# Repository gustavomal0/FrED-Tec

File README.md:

# Proyecto FrED

Este repositorio contiene todos los archivos relacionados con el Proyecto FrED, incluyendo diseños CAD, electrónica y firmware.

## Estructura de directorios

- CAD/: Contiene todos los modelos 3D, dibujos y otros archivos de diseño.
- Electrónica/: Incluye esquemas, diseños de PCB y documentación relacionada.
- Firmware/: Contiene el código fuente y los archivos del firmware.

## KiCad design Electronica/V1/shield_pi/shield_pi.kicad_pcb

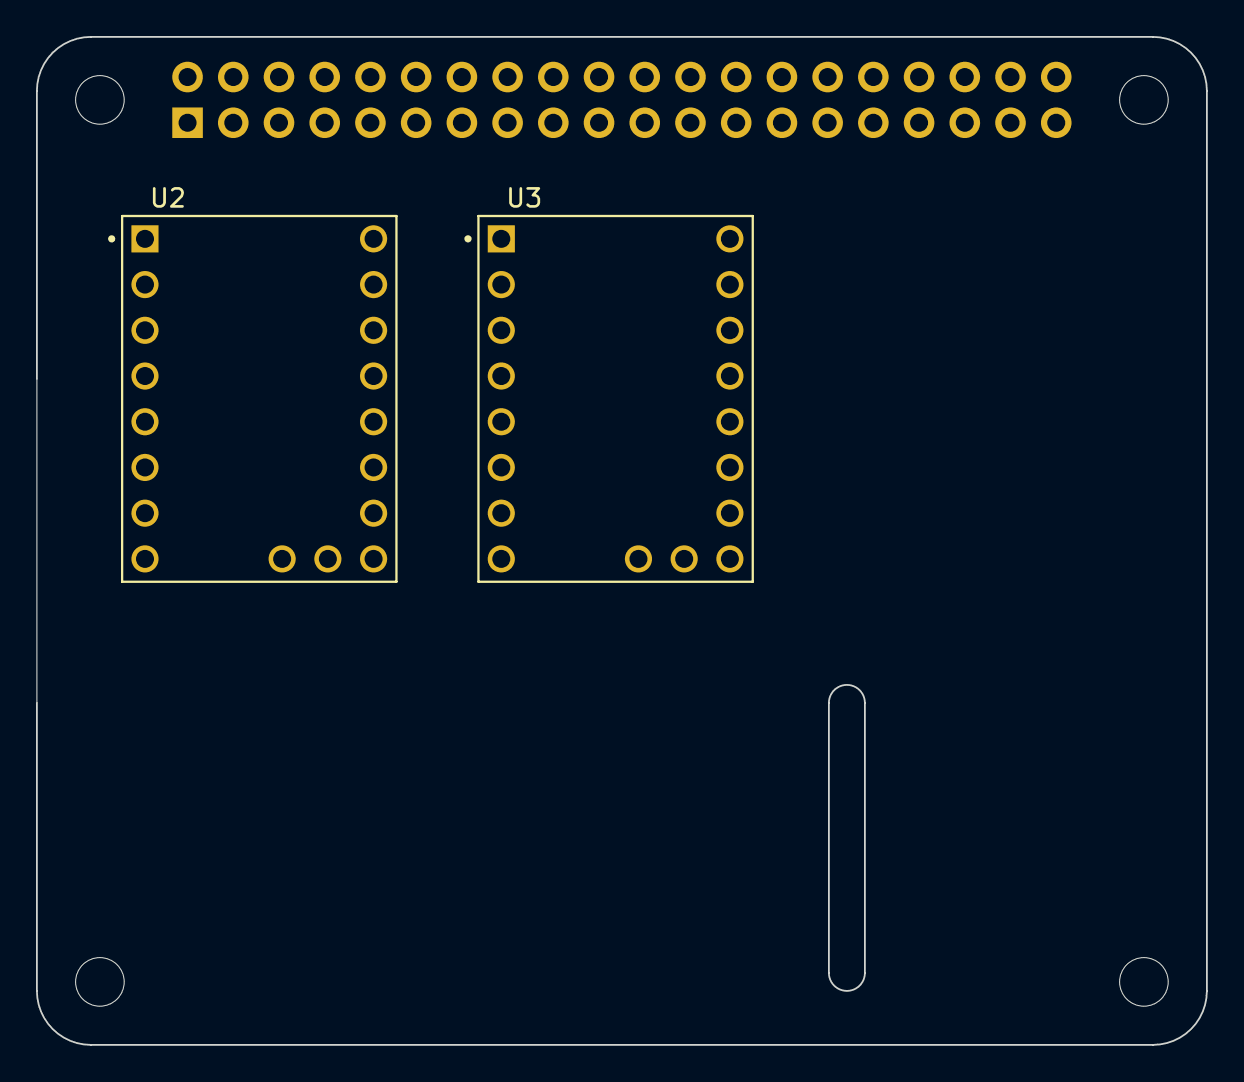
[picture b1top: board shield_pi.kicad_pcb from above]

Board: 2 copper layers, 65.0 x 56.0 mm, 7 parts (1 on the bottom side), 5 nets, no tracks yet.

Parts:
J1: GPIO; PinSocket_2x20_P2.54mm_Vertical
MH1, MH2, MH3, MH4: MountingHole_2.7mm_M2.5
U2, U3: TMC2209_SILENTSTEPSTICK; MODULE_TMC2209_SILENTSTEPSTICK

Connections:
+3V3: J1.1, J1.17
+5V: J1.2, J1.4
GND: J1.6, J1.9, J1.14, J1.20, J1.25, J1.30, J1.34, J1.39
unnamed: U2.1 (GND), U2.7 (GND)
unnamed: U3.1 (GND), U3.7 (GND)

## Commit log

2024-08-28 act .gitignore y readme.md
2024-08-28 carpetas areas
2024-08-28 .gitignore
2024-08-28 readmes
2024-09-19 archivos iniciales, src
2024-09-19 prueba
